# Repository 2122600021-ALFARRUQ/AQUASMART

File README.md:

# AQUA SMART
<div align="center">
    
</div>

## **Supported By:**  
🌟 **Dosen Pengampu:** Akhmad Hendriawan, S.T., M.T.  *(NIP: 197501272002121003)*  
🎓 **Mata Kuliah:** IOT dan Jaringan Sensor  
🎯 **Program Studi:** Sarjana Terapan Teknik Elektronika  
🏫 **Politeknik Elektronika Negeri Surabaya**  

# Daftar Isi

- [Deskripsi](#deskripsi)
- [Buku Panduan](#buku-panduan)
- [Komponen](#komponen)
   * [1. ESP32](#1-esp32)
   * [2. Sensor Ultrasonic](#2-sensor-ultrasonic)
   * [3. Flow Sensor](#3-flow-sensor)
   * [4. Adaptor 12V 2A](#4-adaptor-12v-2a)
   * [5. Solenoid Valve](#5-solenoid-valve)
   * [6. Modul Relay](#6-modul-relay)
- [Diagram Arsitektur](#diagram-arsitektur)
- [Tim Pengembang](#tim-pengembang)
- [Timeline Pengembangan](#timeline-pengembangan)
- [Rincian Pengeluaran Biaya](#rincian-pengeluaran-biaya)
- [Hardware](#hardware)
  * [1. Schematic Rangkaian](#1-schematic-rangkaian)
  * [2. Desain PCB](#2-desain-pcb)
  * [3. 3D Model PCB](#3-3d-model-pcb)
  * [4. Hasil 3D](4-hasil-3d)
- [Software](#software)
  * [1. Flowchart](#1-flowchart)
  * [2. Simulasi Wokwi](#2-simulasi-wokwi)
  * [3. Node-Red](#3-node-red)
  * [4. Sequence Diagram](#4-sequence-diagram)
  * [5. Class Diagram](#5-class-diagram)
- [Web APP](#web-app)
- [Dokumentasi](#dokumentasi)
  * [1. Video Percobaan Pengiriman Data dari ESP32 ke Broker MQTT](#1-video-percobaan-pengiriman-data-dari-esp32-ke-broker-mqtt)
  * [2. Video Simulasi Wokwi](#2-video-simulasi-wokwi)
  * [3. Video Simulasi Aplikasi](#3-video-simulasi-aplikasi)
    * [3.1 Video Simulasi Aplikasi Web](#31-video-simulasi-aplikasi-web)
    * [3.2 Video Simulasi Aplikasi Mobile](#32-video-simulasi-aplikasi-mobile)
  * [4. Video Pengujian Sensor Ultrasonik](#4-video-pengujian-sensor-ultrasonik)
  * [5. Video Pengujian Hardware](#5-video-pengujian-hardware)
  * [6. Video Penggunaan Alat (User)](#6-video-penggunaan-alat-user)
  * [7. Proses Pengerjaan](#7-proses-pengerjaan)
  * [8. Video Pengiklanan](#8-video-pengiklanan)
  * [9. Video Presentasi](#9-video-presentasi)

# Deskripsi
Sistem Monitoring Penggunaan Air Berbasis IoT ini dirancang untuk membantu rumah tangga dalam memantau penggunaan dan ketersediaan air secara real-time. Menggunakan ESP32 sebagai kontroler utama, sistem ini memanfaatkan sensor aliran air (Flow Sensor) untuk melacak jumlah air yang digunakan serta sensor ultrasonik untuk mengukur level air di dalam tangki penyimpanan. Data yang diperoleh akan dikirimkan ke platform cloud Adafruit IO melalui protokol MQTT, di mana pengguna dapat mengaksesnya melalui aplikasi ponsel atau website.

Dengan sistem ini, pengguna dapat mengelola air secara lebih efisien, mencegah kebocoran, dan menerima notifikasi dini ketika air di tangki hampir habis. Sistem juga dapat diperluas untuk memantau beberapa titik pengukuran berbeda di rumah, seperti dapur atau kamar mandi, dengan menambahkan modul tambahan.

# Buku Panduan
[Buku Panduan AquaSmart.pdf](https://github.com/2122600021-ALFARRUQ/AQUASMART/blob/3b80df1f71be8b21b987adbf3e9ceadbd6fab604/Buku%20Panduan%20AquaSmart.pdf)

# Komponen
## 1. ESP32
ESP32 adalah Mikrokontroler System on Chip (SoC) berbiaya rendah dari Espressif Systems, yang juga sebagai pengembang dari SoC ESP8266 yang terkenal dengan NodeMCU. ESP32 adalah penerus SoC ESP8266 dengan menggunakan Mikroprosesor Xtensa LX6 32-bit Tensilica dengan Wi-Fi dan Bluetooth yang terintegrasi.
ESP32 memiliki dua prosesor komputasi, satu prosesor untuk mengelola jaringan WiFi dan Bluetooth, serta satu prosesor lainnya untuk menjalankan aplikasi. Dilengkapi dengan memori RAM yang cukup besar untuk menyimpan data. Fitur yang berguna seperti TCP/IP, HTTP, dan FTP.
Pada proyek ini ESP32 berfungsi sebagai pusat pengendali yang mengumpulkan data dari sensor dan mengirimkannya ke sistem monitoring.

## 2. Sensor Ultrasonic
Sensor ultrasonik merupakan sensor yang menggunakan gelombang ultrasonik. Gelombang ultrasonik yaitu gelombang yang umum digunakan untuk mendeteksi keberadaan suatu benda dengan memperkirakan jarak antara sensor dan benda tersebut. Sensor ini berfungsi untuk mengubah besaran fisis (bunyi) menjadi besaran listrik begitu pula sebaliknya. Gelombang ultrasonik memiliki frekuensi sebesar 20.000 Hz. Bunyi tersebut tidak dapat didengar oleh telinga manusia. Bunyi tersebut dapat didengar oleh hewan tertentu seperti anjing, kelelawar dan kucing. Bunyi gelombang ultrasonik dapat merambat melalui zat cair, padat dan gas. Benda cair merupakan media merambat yang paling baik untuk sensor ultrasonik jika dibandingkan dengan benda padat dan gas. 
Pada proyek ini sensor ultrasonic digunakan untuk mengukur ketinggian air dengan memantulkan gelombang suara ke permukaan air. 

## 3. Flow Sensor
Flow sensor merupakan sensor yang digunakan untuk mengukur aliran cairan seperti gas atau cairan. Flow sensor memanfaatkan sub sistem mekanik dan listrik untuk mengukur perubahan atribut fisik fluida dan menghitung alirannya. Mengukur atribut fisik tergantung pada atribut fluida. Fluida gas, cair dan non-newtonian memiliki perilaku satu sama lain yang sangat berbeda sehingga metode yang digunakan untuk mengukur alirannya juga harus berbeda. Flow sensor bisa dibagi menjadi dua jenis, yaitu contact sensor dan non-contact sensor. Flow contact sensor digunakan dalam aplikasi dimana cairan atau gas yang diukur diperkirakan tidak akan tersumbat di dalam pipa ketika bersentuhan dengan bagian sensor yang bergerak. Sedangkan flow non-contact sensor tidak memiliki bagian yang bergerak dan biasanya digunakan ketika cairan atau gas yang dipantau akan terkontaminasi maupun diubah secara fisik serta bersentuhan dengan bagian yang bergerak. 
Pada proyek ini flow sensor berfungsi untuk mengukur aliran air yang mengalir dalam pipa.

## 4. Adaptor 12V 2A
Adaptor 12V 2A adalah sebuah alat yang digunakan untuk mengubah sumber daya listrik dari AC (arus bolak-balik) ke DC (arus searah), dengan output 12 volt dan kemampuan untuk memberikan arus hingga 2 ampere. Adaptor ini sering digunakan untuk perangkat elektronik seperti router, CCTV, dan berbagai peralatan lainnya yang membutuhkan sumber daya 12V DC. Adaptor 12V 2A digunakan untuk menyediakan daya yang stabil dengan tegangan 12V dan arus 2A. Komponen seperti solenoid valve dan relay membutuhkan daya ini untuk beroperasi. Adaptor memastikan sistem mendapatkan tegangan yang diperlukan tanpa gangguan.

## 5. Solenoid Valve
Solenoid valve adalah katup yang dikendalikan oleh arus AC atau DC melalui coil/selenoida. Katup Solenoid adalah elemen control yang paling sering digunakan dalam sistem fluida. Seperti pada sistem pneumatic, sistem hidrolik atau sistem control mesin memerlukan elemen control otomatis. Katup ini bisa dikendalikan oleh ESP32 untuk membuka atau menutup aliran sesuai kebutuhan.
Solenoid valve akan beroperasi jika coil/kumparan menerima tegangan arus yang sesuai dengan tegangan operasi (kebanyakan tegangan kerja katup solenoid adalah 100/200 VAC dan sebagian besar tegangan operasi pada tegangan DC adalah 12/24 VDC). Dan sebuah pin akan tertarik akibat gaya magnet yang dihasilkan oleh kumparan solenoid. Dan saat pin sitarik ke atas, cairan akan mengalir dengan cepat dari rongga C ke bagian D. Oleh karena itu, tekanan di rongga C berkurang dan tekanan cairan yang masuk akan menaikkan diafragma. Biarkan katup utama terbuka dan cairan mengalir langsung dari A ke F.

## 6. Modul Relay
Modul relay Arduino adalah perangkat keras yang berfungsi untuk mengontrol perangkat listrik eksternal seperti motor, lampu dan peralatan rumah tangga lainnya menggunakan platform Arduino. Modul ini terdiri dari relay dan beberapa komponen pendukung lainnya yang terintegrasi dengan papan sirkuit terpadu (PCB). Sedangkan relay adalah saklar elektronik yang dapat dikontrol secara elektrik. Ketika relay diberikan sinyal listrik, kontaknya akan terbuka atau tertutup, sehingga memungkinkan arus listrik mengalir atau terputus. Pada umumnya, modul relay ini terhubung ke papan Arduino melalui pin digital.
Modul Relay memungkinkan ESP32 mengontrol perangkat tegangan tinggi dengan aman, seperti solenoid valve atau pompa air, melalui sinyal dari mikrokontroler.

# Diagram Arsitektur
<div align="center">
    
</div>

# Tim Pengembang
<div align="center">
    
</div>

# Timeline Pengembangan

| Minggu | Tugas                                           | Tanggal                   |
|--------|-------------------------------------------------|---------------------------|
| 1      | Perencanaan dan pengajuan proposal              | 01-10-2024 s/d 07-10-2024 |
| 2      | Pengembangan hardware dan pemrograman ESP32     | 08-10-2024 s/d 14-10-2024 |
| 3      | Pengujian sistem IoT dan integrasi cloud        | 15-10-2024 s/d 21-10-2024 |
| 4      | Finalisasi dan presentasi proyek                | 22-10-2024 s/d 04-11-2024 |

# Rincian Pengeluaran Biaya

| Item                       | Jumlah | Harga Satuan (Rp) | Total (Rp) |
|---------------------------|--------|-------------------|------------|
| ESP32                     | 1      | 75,000            | 75,000     |
| Sensor Ultrasonic         | 1      | 10,000            | 10,000     |
| Flow Sensor              | 1      | 74,000            | 74,000     |
| Adaptor 12V 2A            | 1      | 16,000            | 16,000     |
| Solenoid Valve              | 1      | 65,000            | 65,000     |
| Modul Relay               | 2      | 8,200            | 16,400     |
| Kabel-Kabel               | 1      | 10,000            | 10,000     |
| Cetak 3D                 | 1      | 200,000                 | 200,000           |
| **Total Biaya**          | -      | -                 | **466,400**|

# Hardware
## 1. SCHEMATIC RANGKAIAN
Berikut ini adalah hasil skematik rangkaian sistem monitoring air menggunakan software Kicad
<div align="center">
    
</div>

## 2. DESAIN PCB
Berikut ini adalah hasil layout rangkaian sistem monitoring air menggunakan software Kicad
<div align="center">
    
</div>

## 3. 3D MODEL PCB
Berikut ini adalah hasil 3D rangkaian sistem monitoring air menggunakan software Kicad
<div align="center">
    
</div>

Link Thingiverse : https://www.thingiverse.com/thing:6853870

Link PCB jadi : https://github.com/2122600021-ALFARRUQ/AQUASMART/tree/10eaccd06828d46e413301323a7a25bb22af950c/Hardware/Foto

## 4. Hasil 3D

# Software

## 1. FLOWCHART
<div align="center">
    
</div>
Flowchart diatas menggambarkan proses kerja sistem monitoring air menggunakan sensor ultrasonic dan rotary encoder. Proses dimulai dengan inisialisasi perangkat keras (setup). Sistem memeriksa apakah waktu tanpa aliran air melebihi ambang batas (threshold). Jika ya, nilai variabel encoderDelay disetel menjadi 1000 ms. Jika tidak, sistem menghitung laju aliran air (flow rate) menggunakan fungsi calculateMovingAverage(). Selanjutnya, sensor ultrasonic diaktifkan melalui fungsi ultrasonicTrigger(), dan persentase level air dihitung menggunakan fungsi ultrasonicCalculate(). Data hasil pengukuran berupa persentase level air dan flow rate ditampilkan pada LCD dan Serial Monitor. Pada sisi interrupt, ketika rotasi terdeteksi oleh rotary encoder, waktu saat ini disimpan dalam variabel timeNow, dan encoderDelay dihitung dari selisih timeNow dan timeLast. Nilai timeNow kemudian disimpan kembali ke timeLast untuk pembaruan data. Proses ini berulang secara kontinu untuk memastikan pengukuran berjalan real-time.

## 2. Simulasi Wokwi
<div align="center">
    
</div>
Simulasi pada gambar di atas menggunakan platform Wokwi bertujuan untuk memastikan bahwa rangkaian dapat berfungsi dengan baik sesuai desain, mulai dari membaca data sensor hingga menampilkan output pada LCD dan mengendalikan modul relay, sehingga meminimalkan potensi kesalahan sebelum implementasi pada perangkat keras sebenarnya

Link : https://wokwi.com/projects/411618765119428609

## 3. NODE-RED
<div align="center">
    
</div>
Gambar di atas menunjukkan diagram alur Node-RED untuk sistem pengelolaan data berbasis IoT dengan topik AQUASMART. Dalam function 1 digunakan untuk mengolah data yang dikirimkan dari MQTT untuk diparsing agar bisa masuk kedalam database aquasmart. Terdapat percabangan dari Node AQUASMART/sensor yang menuju function 2. Data yang disimpan dapat diakses kembali melalui function ini yang mengarah ke node database. Hasil pemrosesan oleh function 3 dikirim ke control/solenoid untuk mengontrol katup solenoid.

## 4. SEQUENCE DIAGRAM
<div align="center">
    
</div>

Sequence diagram pada gambar diatas menunjukkan alur komunikasi antara user, ESP32, sensor, dan broker MQTT dalam sistem IoT. Proses dimulai ketika user mengirimkan perintah ke ESP32 melalui jaringan Wi-Fi. ESP32 memverifikasi koneksi Wi-Fi hingga berhasil, namun jika gagal, sistem meminta user untuk mencoba lagi. Setelah terhubung, ESP32 membaca data dari sensor, lalu data tersebut diproses sebelum dikirim ke broker MQTT untuk diakses lebih lanjut. Diagram ini menunjukkan interaksi yang terorganisir untuk memastikan data dari sensor dapat diteruskan dengan akurat ke server atau aplikasi yang memanfaatkan MQTT sebagai protokol komunikasi.

## 5. CLASS DIAGRAM
<div align="center">
    
</div>

Gambar di atas menujukkan hubungan antar kelas dalam sistem berbasis ESP32 untuk pemantauan dan pengelolaan data. Kelas utama adalah ESP32, yang memiliki fungsi seperti connectWiFi (koneksi ke jaringan Wi-Fi), collectData (pengumpulan data dari sensor), sendToMQTT (mengirim data ke server MQTT), dan syncTime (sinkronisasi waktu menggunakan NTP). ESP32 berinteraksi dengan dua jenis sensor: WaterLevelSensor, yang memiliki fungsi readLevel untuk membaca ketinggian air, dan FlowSensor, yang menggunakan fungsi readFlow untuk mengukur aliran air. Data yang dikumpulkan kemudian dikirim ke MQTTClient, yang bertugas melakukan koneksi (connect), publikasi data (publish), dan langganan ke topik tertentu (subscribe). Selain itu, sinkronisasi waktu dilakukan dengan bantuan NTPClient melalui fungsi syncTime. Diagram ini menunjukkan arsitektur terintegrasi antara pengumpulan data sensor, komunikasi MQTT, dan sinkronisasi waktu.

# Web App
Link Web App Project Aquasmart dapat di lihat di sini : https://aquasmart-fdbackfue8hjdhgg.canadacentral-01.azurewebsites.net/

# Dokumentasi

## 1. Video Percobaan Pengiriman Data dari ESP32 ke Broker MQTT
https://github.com/user-attachments/assets/0b649f9e-3a0d-4be2-93d4-879152762dc5 
## 2. Video Simulasi Wokwi
https://github.com/user-attachments/assets/3788917b-d15c-42b3-9d15-79d57b5753b3 
## 3. Video Simulasi Aplikasi
### 3.1 Video Simulasi Aplikasi Web
https://github.com/user-attachments/assets/d782f18b-91e5-41b1-a5a1-bee070e43c8c
### 3.2 Video Simulasi Aplikasi Mobile
https://github.com/user-attachments/assets/036225ad-1f3f-4121-946e-6db940966c42
## 4. Video Pengujian Sensor Ultrasonik
https://github.com/user-attachments/assets/7d10899d-bf8c-4fc1-9f14-af5eacd0cc40 
## 5. Video Pengujian Hardware
https://github.com/user-attachments/assets/dedbf46f-3d43-4d81-ba96-16eca15a14ef
## 6. Video Penggunaan Alat (User)
https://youtu.be/zm1uCubxG-E
## 7. Proses Pengerjaan

## 8. Video Pengiklanan 
https://github.com/user-attachments/assets/52b6b247-8677-437f-991a-c6e8a309753d 
## 9. Video Presentasi
https://github.com/user-attachments/assets/3ab094f8-9b1d-4ff9-a2a7-7a724e087a73

slide presentasi dapat dilihat pada link berikut : https://github.com/2122600021-ALFARRUQ/AQUASMART/blob/2130463fc0ef71a656cedb03aadac50fb50dbc7b/IOT%20DAN%20JARINGAN%20_compressed.pdf

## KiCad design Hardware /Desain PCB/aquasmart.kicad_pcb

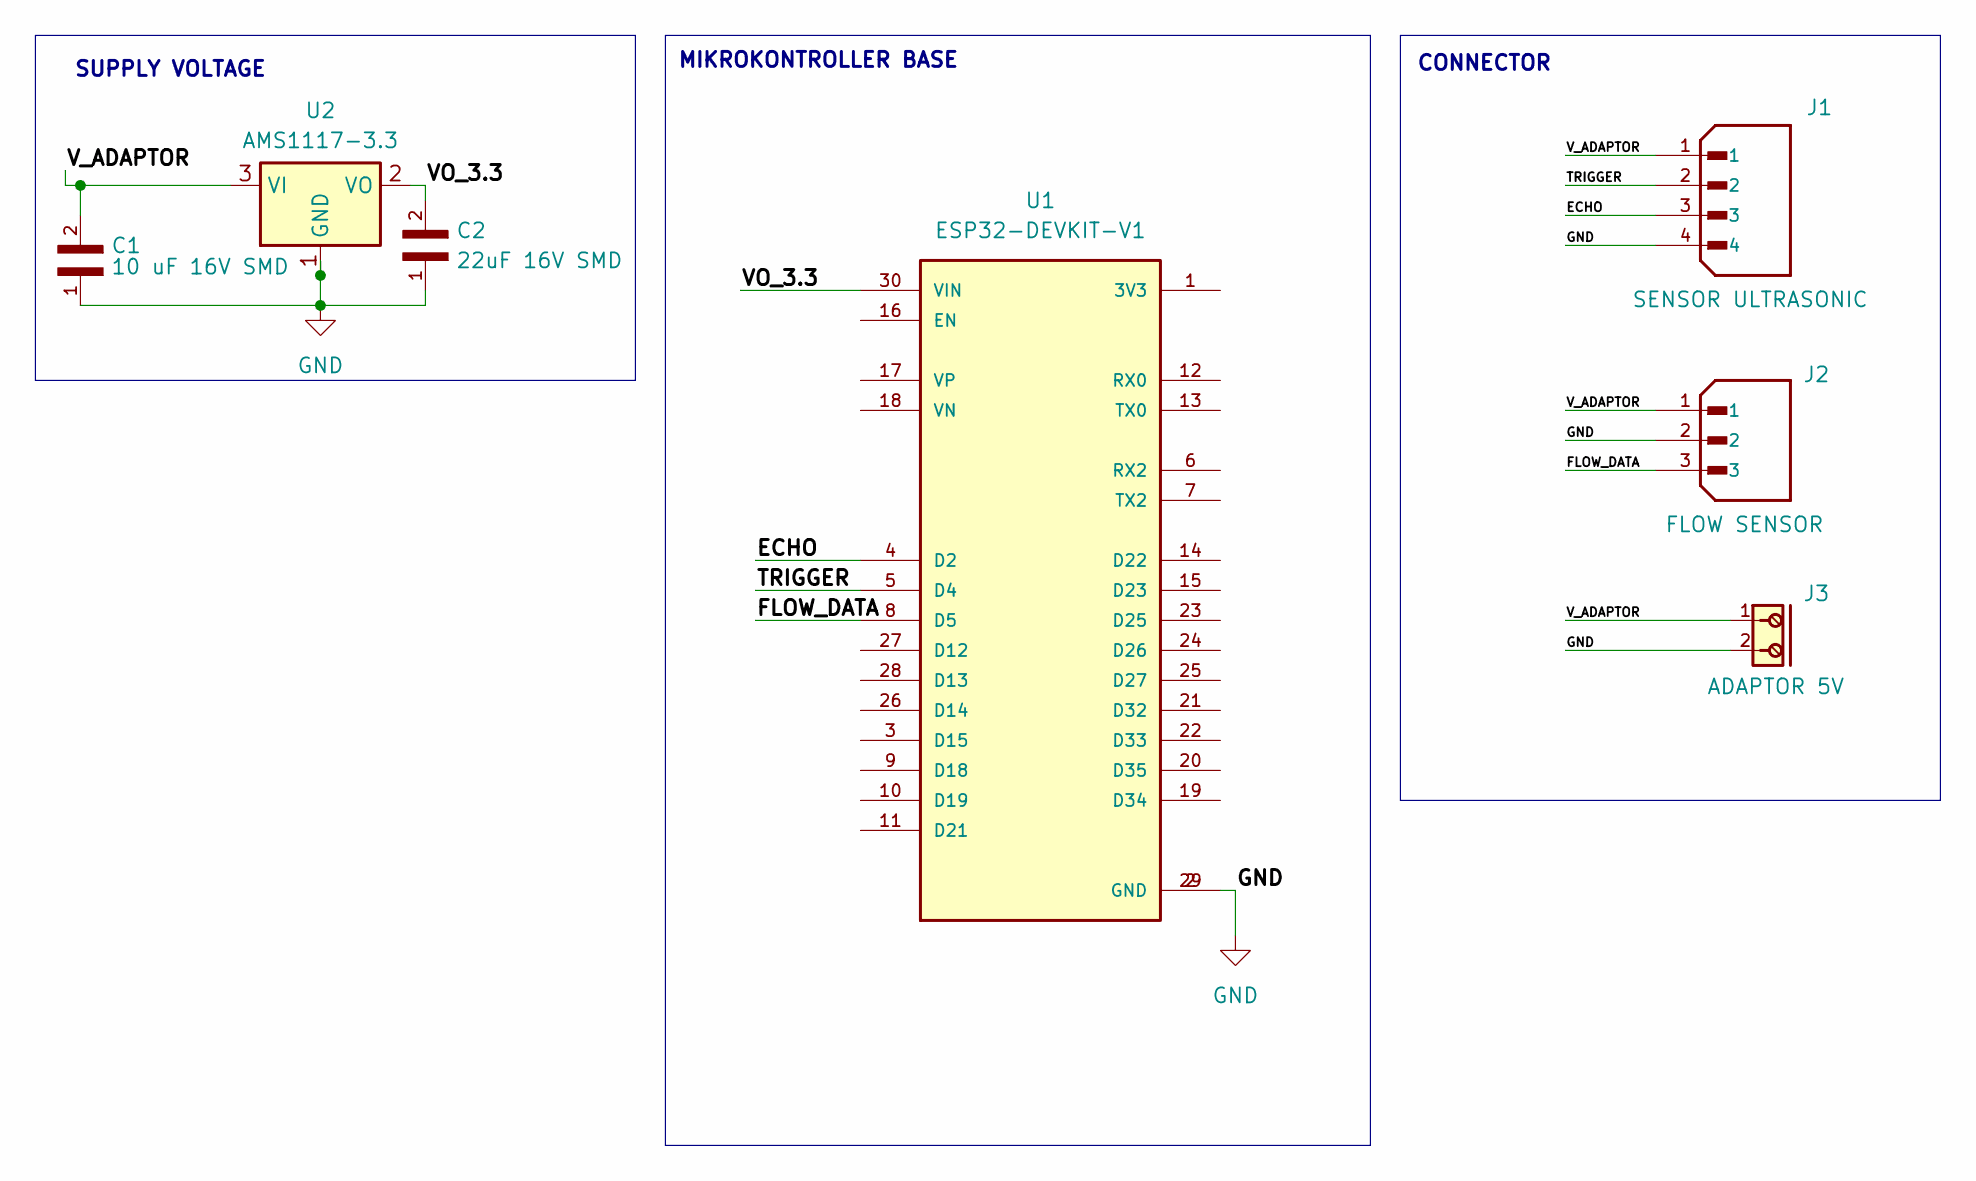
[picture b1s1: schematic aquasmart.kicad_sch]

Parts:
C1: 10 uF 16V SMD; CAPC3216X180N
C2: 22uF 16V SMD; CAPC3225X270N
J1: SENSOR ULTRASONIC; JST_B4B-XH-A_LF__SN_; PARTREV 7/4/21
J2: FLOW SENSOR; JST_B3B-XH-A; PARTREV 7/4/21
J3: ADAPTOR 5V; 691213510002; PART-NUMBER 691213510002
U1: ESP32-DEVKIT-V1; MODULE_ESP32_DEVKIT_V1; PARTREV N/A
U2: AMS1117-3.3; SOT-223-3_TabPin2

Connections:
/ECHO: J1.3, U1.4 (D2)
/FLOW_DATA: J2.3, U1.8 (D5)
/TRIGGER: J1.2, U1.5 (D4)
/VO_3.3: C2.2, U1.30 (VIN), U2.2 (VO)
/V_ADAPTOR: C1.2, J1.1, J2.1, J3.1, U2.3 (VI)
GND: C1.1, C2.1, J1.4, J2.2, J3.2, U1.2 (GND), U1.29 (GND), U2.1 (GND)

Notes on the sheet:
CONNECTOR
SUPPLY VOLTAGE
MIKROKONTROLLER BASE

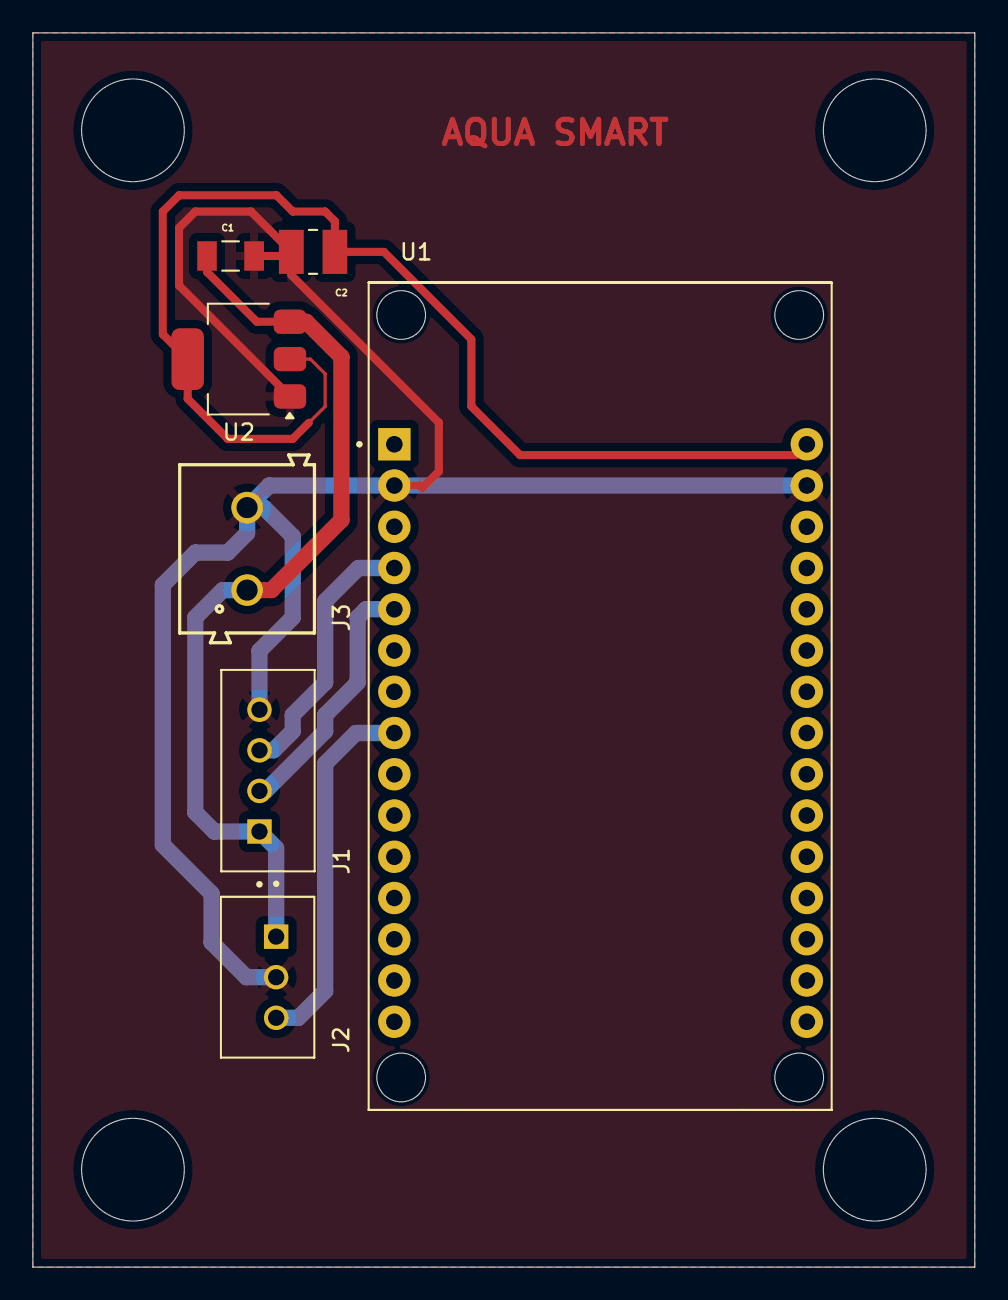
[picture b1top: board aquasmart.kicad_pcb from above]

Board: 2 copper layers, 58.0 x 76.0 mm, 7 parts (0 on the bottom side), 6 nets.

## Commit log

2024-10-13 Create diisi pcb kicad
2024-10-13 Add Desain PCB Kicad
2024-10-13 Create logo
2024-10-13 Penambahan file Source Code untuk ESP32
2024-10-13 Rename Software/ESP32 Source Code/Link Wokwi.md to Software/Link Wokwi.md
    Penambahan link simulasi Wokwi
2024-10-13 Create Libraries directory & Libraries.md
    Menambahkan daftar library yang digunakan beserta link github masing-masing library
2024-10-13 Menambahkan file Library
    Menambahkan file untuk library:
    - LiquidCrystal_I2C
    - Ai_Esp32_Rotary_Encoder
2024-10-13 Ganti lokasi link wokwi dari Software ke main
2024-10-13 Create temp
2024-10-13 Menambahkan Flowchart Program untuk ESP32
2024-10-13 Create Link Prototype
2024-10-13 Menambahkan Flowchart untuk Program ESP32
2024-10-13 Delete Software/ESP32 Source Code/Flowchart Program ESP32.svg
    Hapus Flowchart untuk perbaikan
2024-10-13 Upload ganti Flowchart Program ESP32
2024-10-13 Upload Ganti Flowchart Program
2024-10-14 Fixed invalid file paths
2024-10-14 Rename aquasmart-B_Cu.pdf to aquasmart-B_Cu.pdf
2024-10-14 Rename aquasmart-F_Cu.pdf to aquasmart-F_Cu.pdf
2024-10-14 Rename aquasmart_3D_PCB.png to aquasmart_3D_PCB.png
2024-10-14 Rename aquasmart_sch.pdf to aquasmart_sch.pdf
2024-10-14 Rename Link Prototype to Link Prototype
2024-10-14 Rename base.png to base.png
2024-10-14 Rename premium.png to premium.png
2024-10-14 Rename Link Prototype to Link_Prototype
2024-10-14 Rename temp to temp
2024-10-14 Rename Ai_Esp32_Rotary_Encoder.zip to Ai_Esp32_Rotary_Encoder.zip
2024-10-14 Rename Libraries.md to Libraries.md
2024-10-14 Rename LiquidCrystal_I2C.zip to LiquidCrystal_I2C.zip
2024-10-14 Rename Flowchart Program ESP32.svg to Flowchart Program ESP32.svg
2024-10-14 Rename Project_AquaSmart.ino to Project_AquaSmart.ino
2024-10-14 Rename AQUA SMART (1).png to AQUA_SMART (1).png
2024-10-14 Rename logo to logo-create
2024-10-14 Rename LICENSE to LICENSE2
2024-10-14 Rename Link Wokwi.md to Link_Wokwi.md
2024-10-14 Rename README.md to READMEE.md
2024-10-14 Rename LICENSE2 to LICENSE
2024-10-14 Rename READMEE.md to README.md
2024-10-14 Rename logo-create to logo
2024-10-14 Rename Flowchart Program ESP32.svg to Flowchart_Program_ESP32.svg
2024-10-14 Added Rangkaian_Wokwi.jpeg
2024-10-14 Rename Rangkaian_wokwii.jpeg to Rangkaian_Wokwi.jpeg
2024-10-14 Upload foto schematic & design pcb
2024-10-14 Create p
2024-10-14 menambahkan file case 3D
2024-10-14 foto case setiap sisi
2024-10-20 Update Project_AquaSmart.ino
    Menambahkan fungsi untuk mendeteksi level air dan menyalakan/mematikan Pompa Air secara otomatis. Juga ditambahkan fungsi untuk mengontrol Solenoid Valve untuk menyambung/putus aliran air.
2024-10-20 Delete Software/ESP32_Source_Code/Rangkaian_Wokwi.jpeg
    update rangkaian
2024-10-20 Delete Software/ESP32_Source_Code/Rangkaian_Wokwi.jpg
    salah penamaan
2024-10-20 Upload gambar rangkaian wokwi yang ter-update
2024-10-20 Create Diagram Arsitektur
2024-10-20 Update README.md
    Mengupdate konsep diagram arsitektur dengan menambahkan solenoid dan pompa
2024-10-20 Update README.md
    Menambahkan link youtube dengan fitur terbaru
2024-10-21 Update README.md
    Menambahkan daftar isi dan mengupdate RAB
2024-10-21 Menambahkan File Revisi Desain PCB
    menambahkan 2 header untuk relay solenoid dan pompa air
2024-10-21 update gambar Desain PCB pada README.md
    menambahkan gambar terbaru dari revisi gambar schematic, layout, 3d pcb
2024-10-21 Create progres1.txt
    menambahkan folder untuk progres 1
2024-10-21 Create progres 2
    penambahan mounting
2024-10-21 penambahan mounting
    penambahan 3 mounting dan mengubah ukuran box
2024-10-21 foto desain progres 2
2024-10-27 Create Progres 3
2024-10-27 Rename Progres 3 to Progres 3.main
2024-10-27 Add files via upload
    penambahan dudukan mur dan jarak konnector
2024-11-03 menambahkan foto real pcb yang sudah jadi
    pcb sudah dicetak, dipasangi komponen dan disolder dengan baik....siap dipasangkan ke casingnya/ wadahnya
2024-11-03 Update Project_AquaSmart.ino
    Added MQTT Functionality:
    + Sending Flow Rate Value
    + Sending Water Level Value
    + Solenoid Control from Cloud
2024-11-04 Create Finaly
2024-11-04 hardware done
2024-11-04 Update Project_AquaSmart.ino
    Added MQTT Functionality:
    + Sending Flow Rate Value
    + Sending Water Level Value
    + Sending Water Pump State
    + Sending Solenoid Valve State
    + Solenoid Control from Cloud
2024-11-04 Update README.md
    Menambahkan Struktur Manajemen Team
2024-11-06 Update README.md
    Menambahkan video aplikasi
2024-11-07 Update README.md
    perbarui daftar isi
2024-11-07 Update README.md
    Update deskripsi komponen
2024-11-07 Update README.md
    Update lebih rapi
2024-11-07 Update README.md
    update video
2024-11-07 Rename Hardware/Final (1).jpg to Hardware/Final/Final (1).jpg
2024-11-07 Rename Hardware/Final (3).jpg to Hardware/Final/Final (3).jpg
2024-11-07 Rename Hardware/Final (4).jpg to Hardware/Final/Final (4).jpg
2024-11-07 Rename Hardware/Final (5).jpg to Hardware/Final/Final (5).jpg
2024-11-07 Rename Hardware/Final (6).jpg to Hardware/Final/Final (6).jpg
2024-11-08 Pengujian Keakuratan Sensor Ultrasonik
    Pengujian keakuratan sensor ultrasonik dilakukan dengan menempatkan objek pada jarak yang telah diketahui di depan sensor dengan beberapa variasi jarak. Pengukuran diulang beberapa kali pada setiap j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
2024-11-08 Update README.md
    Penambahan Video Pengujian Sensor Ultrasonik
2024-11-08 Update README.md
    tambahan flyer
2024-11-08 Rename Screenshot (198).png to Design_nodered.png
2024-11-10 Update README.md
    Penambahan Video Pengiriman Data
2024-11-11 Add files via upload
    class diagram
2024-11-11 Add files via upload
    squance diagram
2024-11-17 Rename squance.png to sequence.png
2024-11-17 rename
2024-11-21 Update README.md
    Revisi flyer
2024-11-21 Update README.md
    Penambahan Video Aplikasi
2024-11-21 Update README.md
    penambahan dokumentasi pengerjaan
2024-11-21 Update README.md
    Penambahan Video Presentasi dan Pengiklanan
2024-11-24 Update program website
    + Menambahkan fungsi agar website dan database kompatibel dengan webhosting Microsoft Azure
    + Fix untuk fungsi tampilan kondisi (state) dari Solenoid dan Pompa Air
    + Menambahkan fungsi agar dapat melakukan kontrol Solenoid dari web
2024-11-24 Added NodeRed file
    + Node Red Flow ditambahkan fungsi untuk dapat mengirimkan data ke Hardware untuk menyalakan/mematikan Solenoid
2024-11-24 Menambahkan gambar Flow NodeRed Terbaru
2024-11-24 Update README.md
    1. menambahkan bagian supporty by
    2. menambahkan daftar isi link video penggunaan alat beserta update daftar isinya
2024-11-27 Update README.md
    Penambahan video pengujian hardware
2024-12-02 Update README.md
    1. menambahkan penjelasan deskriptif dari flowchart, simulasi wokwi, node red, sequence diagram, class diagram,
    2. menambahkan link video penggunaan alat dari sudut pandang user
2024-12-02 Menambahkan Source Code berbasis PlatformIO
    + Menambahkan fitur Wifi Manager
    > Meng-input kredensial Wifi pertama kali
    > Mengganti kredensial Wifi dengan menekan button di hardware
    > Mengganti kredensial Wifi jika tidak ada yang bisa di connect atau password/SSID salah
    + Menambahkan fungsi untuk bekerja dengan Wifi Manager
2024-12-02 Slide Presentasi
2024-12-02 Buku Panduan AquaSmart
2024-12-02 Update README.md
    Penambahan Buku Panduan
2024-12-02 Update README.md
    Penambahan link thingiverse dan pcb jadi
2024-12-02 Update README.md
    Penambahan foto 3d alat
